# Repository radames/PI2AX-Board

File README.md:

# PI2AX-Board

Little cheap converter for Raspberry PI and Dynamixel Motors based on

[How to drive Dynamixel AX-12A servos (with a RaspberryPi](http://www.instructables.com/id/How-to-drive-Dynamixel-AX-12A-servos-with-a-Raspbe/)

for the project [Memememe](http://memememememememe.me/)

### Components
* [SN74LVC2G241](http://uk.farnell.com/webapp/wcs/stores/servlet/ProductDisplay?catalogId=15001&langId=44&urlRequestType=Base&partNumber=2334889&storeId=10151)
* 10k Resistor [0805](uk.farnell.com/webapp/wcs/stores/servlet/ProductDisplay?catalogId=15001&langId=44&urlRequestType=Base&partNumber=2073612&storeId=10151)
* Molex [SPOX 5267](http://uk.farnell.com/webapp/wcs/stores/servlet/ProductDisplay?catalogId=15001&langId=44&urlRequestType=Base&partNumber=9979620&storeId=10151)
* [Pins Rows](http://uk.farnell.com/webapp/wcs/stores/servlet/ProductDisplay?catalogId=15001&langId=44&urlRequestType=Base&partNumber=1803928&storeId=10151)

## Schematic

[pdf](PI2AX.pdf)

## Board

## Final

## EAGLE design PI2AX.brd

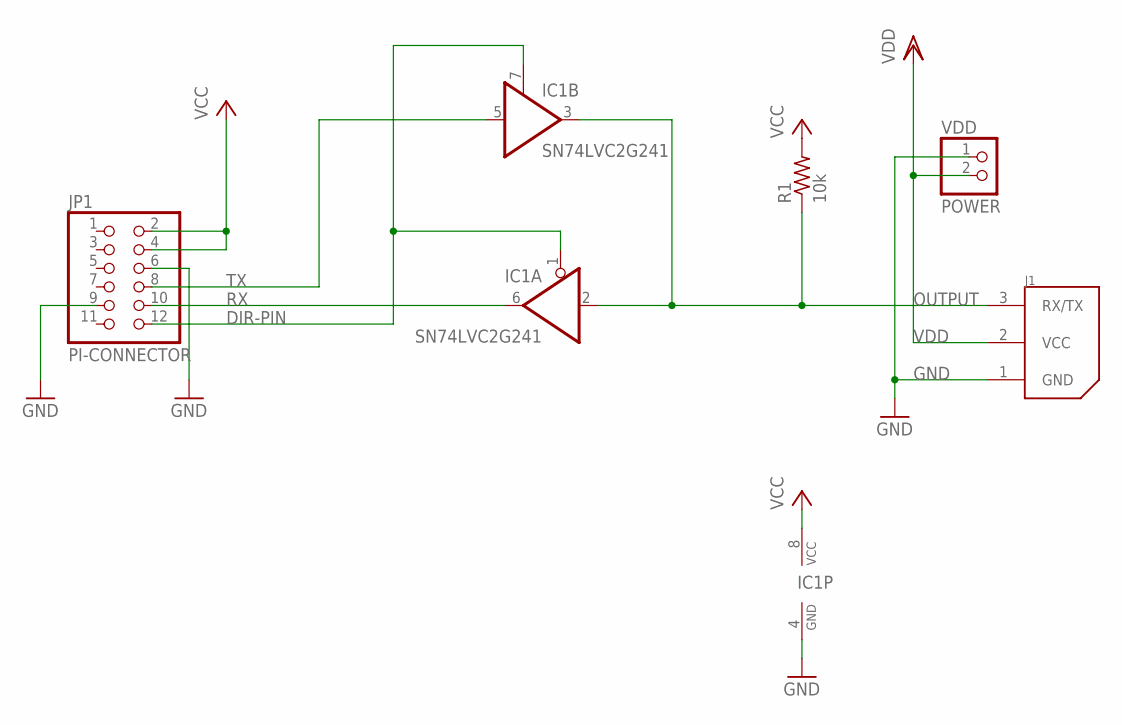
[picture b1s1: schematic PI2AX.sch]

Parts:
IC1: SN74LVC2G241; SSOP08
J1: 22-03-5035; 5267-3
JP1: PI-CONNECTOR; 2X06
R1: 10k; R0805
VDD: POWER; 1X02

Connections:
DIR-PIN: IC1.1 (OE), IC1.7 (OE), JP1.12
GND: IC1.4 (GND), J1.1 (GND), JP1.6, JP1.9, VDD.1
OUTPUT: IC1.2 (I), IC1.3 (O), J1.3 (RX/TX), R1.1
RX: IC1.6 (O), JP1.10
TX: IC1.5 (I), JP1.8
VCC: IC1.8 (VCC), JP1.2, JP1.4, R1.2
VDD: J1.2 (VCC), VDD.2

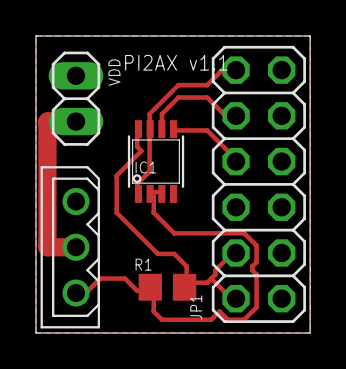
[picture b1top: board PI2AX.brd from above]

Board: 2 copper layers, 15.2 x 16.5 mm, 5 parts (0 on the bottom side), 7 nets.

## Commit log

2017-01-09 adding schematics
2017-01-09 images
2017-01-23 revised v1.1, molex connector fixed
2017-02-13 final images and updated pdf
